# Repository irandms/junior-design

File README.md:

# junior-design
ECE 341 Junior Design - Final Project - Bluetooth controlled AC switch

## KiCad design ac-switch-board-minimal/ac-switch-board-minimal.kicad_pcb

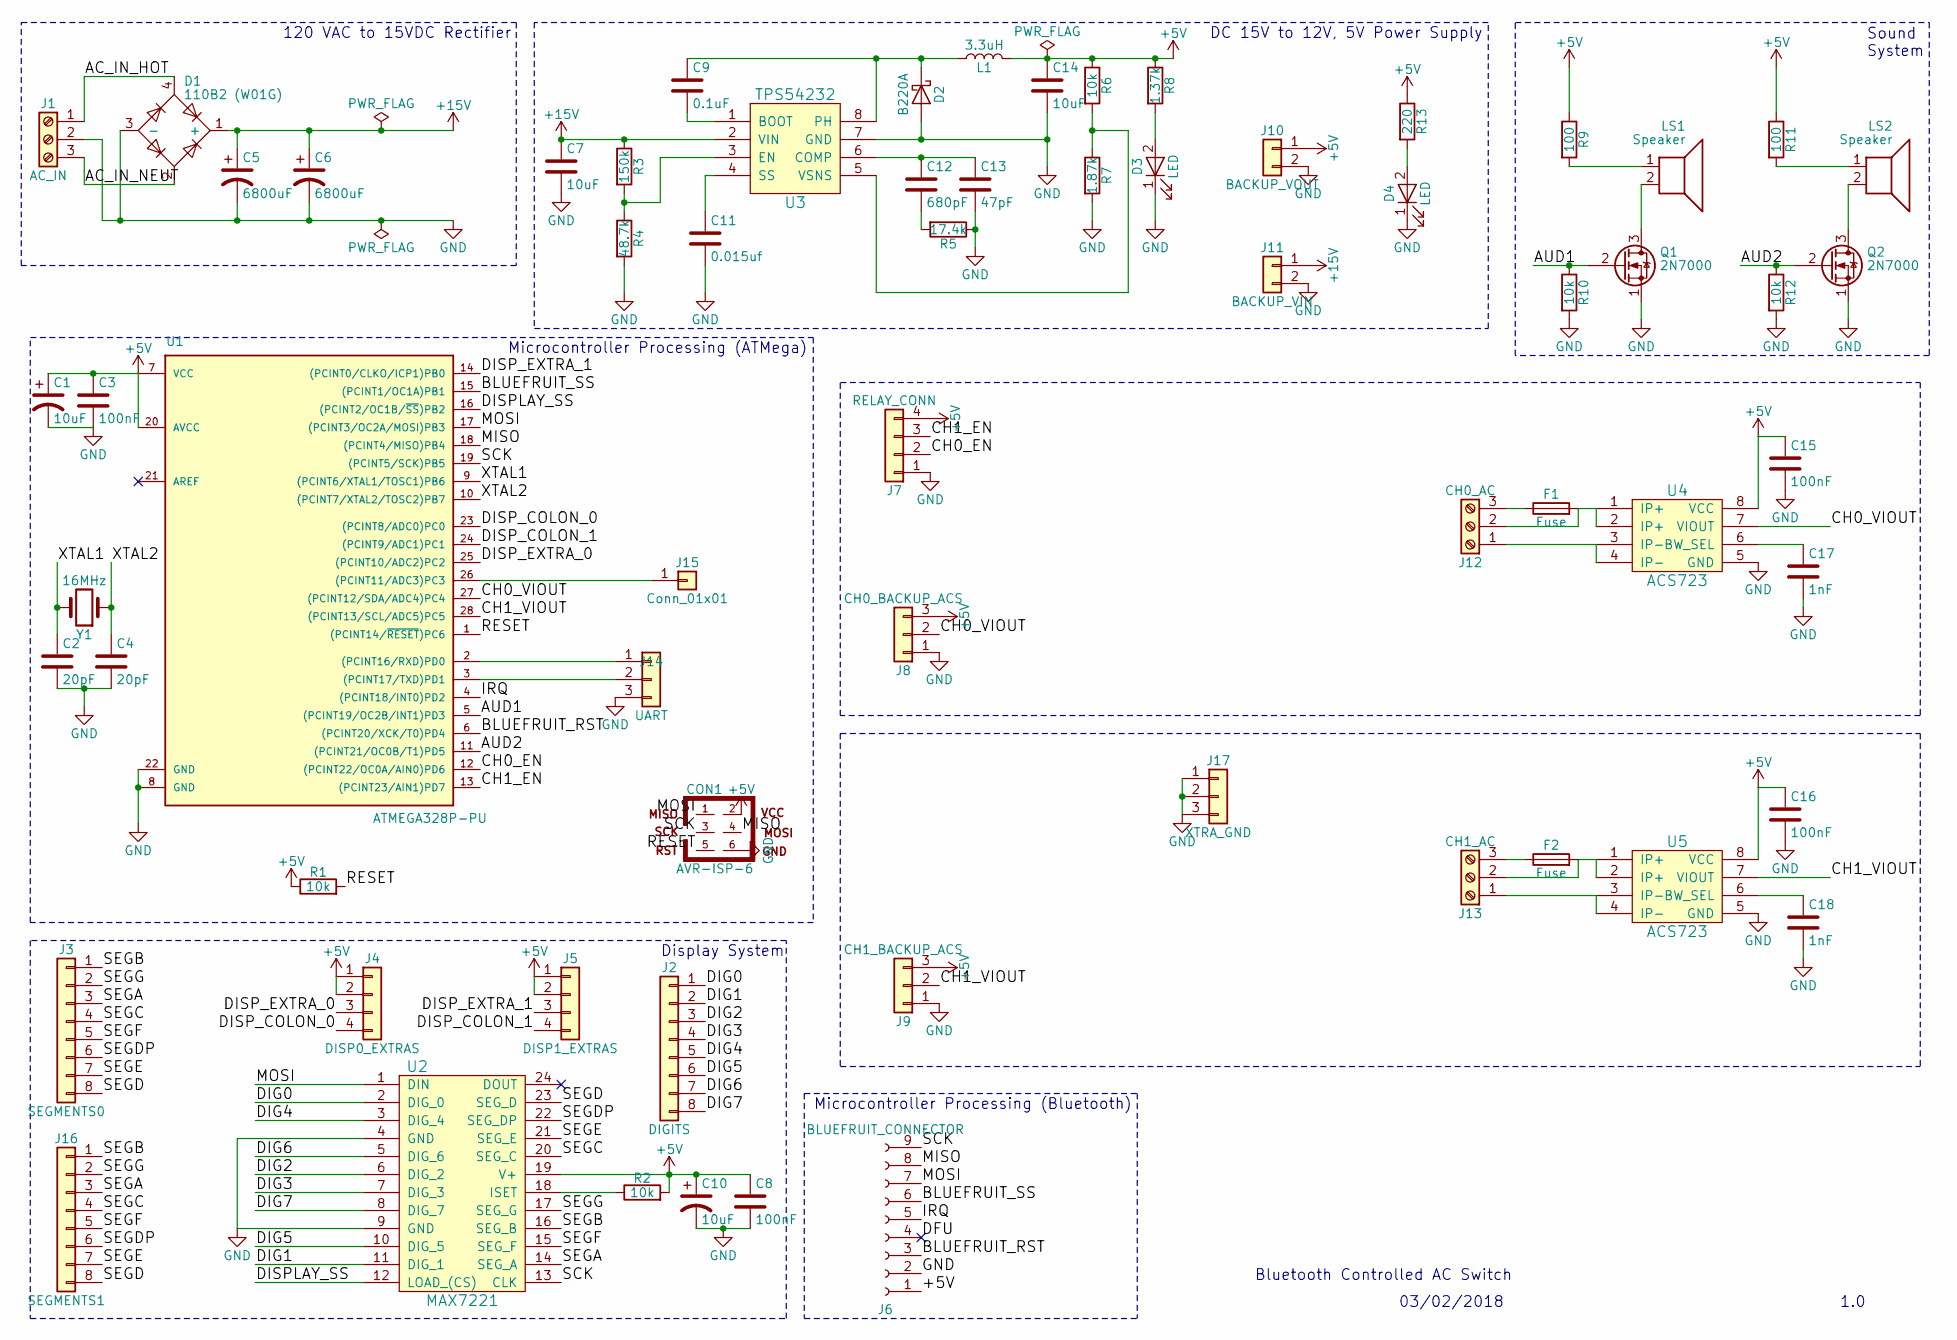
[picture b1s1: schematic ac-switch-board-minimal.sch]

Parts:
C1, C10: 10uF; CP_Elec_4x4.5; MPN EEE-1VA100WR; DigiKey PCE3948CT-ND
C2: 20pF; C_0603; MPN CL10C200JB8NCNC; DigiKey 1276-2220-1-ND
C3, C8, C15, C16: 100nF; C_1206_HandSoldering; MPN C1206C104K5RAC7867; DigiKey 399-1249-1-ND
C4: 20pF; C_0603
C5, C6: 6800uF; CP_Radial_D18.0mm_P7.50mm; MPN EEU-HD1V682; DigiKey P15173-ND
C7: 10uF; C_1206_HandSoldering; MPN C1206C106M3PACTU; DigiKey 399-8153-1-ND
C9: 0.1uF; C_1206_HandSoldering; MPN C1206C104K5RAC7867; DigiKey 399-1249-1-ND
C11: 0.015uf; C_0805_HandSoldering; MPN GRM2195C1H153JA01D; DigiKey 490-1643-1-ND
C12: 680pF; C_0805_HandSoldering; MPN CC0805JRNPO9BN681; DigiKey 311-1121-1-ND
C13: 47pF; C_0805_HandSoldering; MPN CC0805JRNPO9BN470; DigiKey 311-1107-1-ND
C14: 10uF; C_1206_HandSoldering; MPN CL31B106MOHNNNE; DigiKey 1276-6641-1-ND
C17, C18: 1nF; C_0805_HandSoldering; MPN C0805C102K5RACTU; DigiKey 399-1147-1-ND
CON1: AVR-ISP-6; IDC_Header_Straight_6pins
D1: 110B2 (W01G); Diode_Bridge_Round_D8.9mm; MPN W01G-E4/51; DigiKey W01G-E4/51GI-ND
D2: B220A; D_SMA; MPN B220A-13-F; DigiKey B220A-FDICT-ND
D3: LED; LED_0603_HandSoldering; MPN SML-D12V1WT86; DigiKey SML-D12V1WT86CT-ND
D4: LED; Pin_Header_Straight_1x02_Pitch2.54mm
F1, F2: Fuse; Fuseholder5x20_horiz_SemiClosed_Casing10x25mm
J1: AC_IN; AK300-3
J2: DIGITS; Pin_Header_Straight_1x08_Pitch2.54mm
J3: SEGMENTS0; Pin_Header_Straight_1x08_Pitch2.54mm
J4: DISP0_EXTRAS; Pin_Header_Straight_1x04_Pitch2.54mm
J5: DISP1_EXTRAS; Pin_Header_Straight_1x04_Pitch2.54mm
J6: BLUEFRUIT_CONNECTOR; Pin_Header_Straight_1x09_Pitch2.54mm
J7: RELAY_CONN; Pin_Header_Straight_1x04_Pitch2.54mm
J8: CH0_BACKUP_ACS; Pin_Header_Straight_1x03_Pitch2.54mm
J9: CH1_BACKUP_ACS; Pin_Header_Straight_1x03_Pitch2.54mm
J10: BACKUP_VOUT; Pin_Header_Straight_1x02_Pitch2.54mm
J11: BACKUP_VIN; Pin_Header_Straight_1x02_Pitch2.54mm
J12: CH0_AC; AK300-3
J13: CH1_AC; AK300-3
J14: UART; Pin_Header_Straight_1x03_Pitch2.54mm
J15: Conn_01x01; Pin_Header_Straight_1x01_Pitch2.54mm
J16: SEGMENTS1; Pin_Header_Straight_1x08_Pitch2.54mm
J17: XTRA_GND; Pin_Header_Straight_1x03_Pitch2.54mm
L1: 3.3uH; L_Sumida_4.9x4.9mm_diag; MPN CDRH4D28CLDNP-3R3PC; DigiKey 308-2037-1-ND
LS1, LS2: Speaker; Pin_Header_Straight_1x02_Pitch2.54mm
Q1, Q2: 2N7000; TO-92_Molded_Narrow
R1, R2, R6, R10, R12: 10k; R_0805_HandSoldering; MPN ERA-6AEB103V; DigiKey P10KDACT-ND
R3: 150k; R_0805_HandSoldering; MPN RR1220P-154-D; DigiKey RR12P150KDCT-ND
R4: 48.7k; R_0805_HandSoldering; MPN RC0805FR-0748K7L; DigiKey 311-48.7KCRCT-ND
R5: 17.4k; R_0805_HandSoldering; MPN RC0805FR-0717K4L; DigiKey 311-17.4KCRCT-ND
R7: 1.87k; R_0805_HandSoldering; MPN RC0805FR-071K87L; DigiKey 311-1.87KCRCT-ND
R8: 1.37k; R_0805_HandSoldering; MPN RC0805FR-071K37L; DigiKey 311-1.37KCRCT-ND
R9, R11: 100; R_Axial_DIN0207_L6.3mm_D2.5mm_P5.08mm_Vertical
R13: 220; R_0805_HandSoldering; MPN ESR10EZPJ221; DigiKey RHM220KCT-ND
U1: ATMEGA328P-PU; DIP-28_W7.62mm_Socket
U2: MAX7221; DIP-24_W7.62mm_Socket
U3: TPS54232; SOIC-8-N; MPN TPS54232DR; DigiKey 296-39414-1-ND
U4, U5: ACS723; SOIC-8-N; MPN ACS723LLCTR-05AB-T; DigiKey 620-1641-1-ND
Y1: 16MHz; Crystal_HC49-4H_Vertical

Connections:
+5V: C1.1, C3.1, C8.1, C10.1, C14.1, C15.1, C16.1, CON1.2, J4.1, J4.2, J5.1, J5.2, J6.1, J7.4, J8.3, J9.3, J10.1, L1.2, R1.1, R2.2, R6.1, R8.1, R9.1, R11.1, R13.1, U1.7 (VCC), U1.20 (AVCC), U2.19 (V+), U4.8 (VCC), U5.8 (VCC)
+15V: C5.1, C6.1, C7.1, D1.1 (+), J11.1, R3.1, U3.2 (VIN)
/AC_IN_HOT: D1.4, J1.1
/AC_IN_NEUT: D1.2, J1.3
/AUD1: Q1.2 (G), R10.1, U1.5 ((PCINT19/OC2B/INT1)PD3)
/AUD2: Q2.2 (G), R12.1, U1.11 ((PCINT21/OC0B/T1)PD5)
/BLUEFRUIT_RST: J6.3, U1.6 ((PCINT20/XCK/T0)PD4)
/BLUEFRUIT_SS: J6.6, U1.15 ((PCINT1/OC1A)PB1)
/CH0_EN: J7.2, U1.12 ((PCINT22/OC0A/AIN0)PD6)
/CH0_VIOUT: J8.2, U1.27 ((PCINT12/SDA/ADC4)PC4), U4.7 (VIOUT)
/CH1_EN: J7.3, U1.13 ((PCINT23/AIN1)PD7)
/CH1_VIOUT: J9.2, U1.28 ((PCINT13/SCL/ADC5)PC5), U5.7 (VIOUT)
/DFU: J6.4
/DIG0: J2.1, U2.2 (DIG_0)
/DIG1: J2.2, U2.11 (DIG_1)
/DIG2: J2.3, U2.6 (DIG_2)
/DIG3: J2.4, U2.7 (DIG_3)
/DIG4: J2.5, U2.3 (DIG_4)
/DIG5: J2.6, U2.10 (DIG_5)
/DIG6: J2.7, U2.5 (DIG_6)
/DIG7: J2.8, U2.8 (DIG_7)
/DISPLAY_SS: U1.16 ((PCINT2/OC1B/~SS~)PB2), U2.12 (LOAD_(CS))
/DISP_COLON_0: J4.4, U1.23 ((PCINT8/ADC0)PC0)
/DISP_COLON_1: J5.4, U1.24 ((PCINT9/ADC1)PC1)
/DISP_EXTRA_0: J4.3, U1.25 ((PCINT10/ADC2)PC2)
/DISP_EXTRA_1: J5.3, U1.14 ((PCINT0/CLKO/ICP1)PB0)
/IRQ: J6.5, U1.4 ((PCINT18/INT0)PD2)
/RESET: CON1.5, R1.2, U1.1 ((PCINT14/~RESET~)PC6)
/SCK: CON1.3, J6.9, U1.19 ((PCINT5/SCK)PB5), U2.13 (CLK)
/SEGA: J3.3, J16.3, U2.14 (SEG_A)
/SEGB: J3.1, J16.1, U2.16 (SEG_B)
/SEGC: J3.4, J16.4, U2.20 (SEG_C)
/SEGD: J3.8, J16.8, U2.23 (SEG_D)
/SEGDP: J3.6, J16.6, U2.22 (SEG_DP)
/SEGE: J3.7, J16.7, U2.21 (SEG_E)
/SEGF: J3.5, J16.5, U2.15 (SEG_F)
/SEGG: J3.2, J16.2, U2.17 (SEG_G)
/XTAL1: C2.1, U1.9 ((PCINT6/XTAL1/TOSC1)PB6), Y1.2
/XTAL2: C4.1, U1.10 ((PCINT7/XTAL2/TOSC2)PB7), Y1.1
GND: C1.2, C2.2, C3.2, C4.2, C5.2, C6.2, C7.2, C8.2, C10.2, C11.2, C13.2, C14.2, C15.2, C16.2, C17.2, C18.2, CON1.6, D1.3 (-), D2.2 (A), D3.1 (K), D4.1 (K), J1.2, J6.2, J7.1, J8.1, J9.1, J10.2, J11.2, J14.3, J17.1, J17.2, J17.3, Q1.1 (S), Q2.1 (S), R4.2, R5.1, R7.2, R10.2, R12.2, U1.8 (GND), U1.22 (GND), U2.4 (GND), U2.9 (GND), U3.7 (GND), U4.5 (GND), U5.5 (GND)
unnamed: C9.1, D2.1 (K), L1.1, U3.8 (PH)
unnamed: C9.2, U3.1 (BOOT)
unnamed: C11.1, U3.4 (SS)
unnamed: C12.1, C13.1, U3.6 (COMP)
unnamed: C12.2, R5.2
unnamed: C17.1, U4.6 (BW_SEL)
unnamed: C18.1, U5.6 (BW_SEL)
unnamed: D3.2 (A), R8.2
unnamed: D4.2 (A), R13.2
unnamed: F1.1, J12.3
unnamed: F1.2, J12.2, U4.1 (IP+), U4.2 (IP+)
unnamed: F2.1, J13.3
unnamed: F2.2, J13.2, U5.1 (IP+), U5.2 (IP+)
unnamed: J12.1, U4.3 (IP-), U4.4 (IP-)
unnamed: J13.1, U5.3 (IP-), U5.4 (IP-)
unnamed: J14.1, U1.2 ((PCINT16/RXD)PD0)
unnamed: J14.2, U1.3 ((PCINT17/TXD)PD1)
unnamed: J15.1, U1.26 ((PCINT11/ADC3)PC3)
unnamed: LS1.1, R9.2
unnamed: LS1.2, Q1.3 (D)
unnamed: LS2.1, R11.2
unnamed: LS2.2, Q2.3 (D)
unnamed: R2.1, U2.18 (ISET)
unnamed: R3.2, R4.1, U3.3 (EN)
unnamed: R6.2, R7.1, U3.5 (VSNS)

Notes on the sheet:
Bluetooth Controlled AC Switch
03/02/2018
1.0
Microcontroller Processing (ATMega)
Microcontroller Processing (Bluetooth)
Display System
Sound System
120 VAC to 15VDC Rectifier
DC 15V to 12V, 5V Power Supply

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
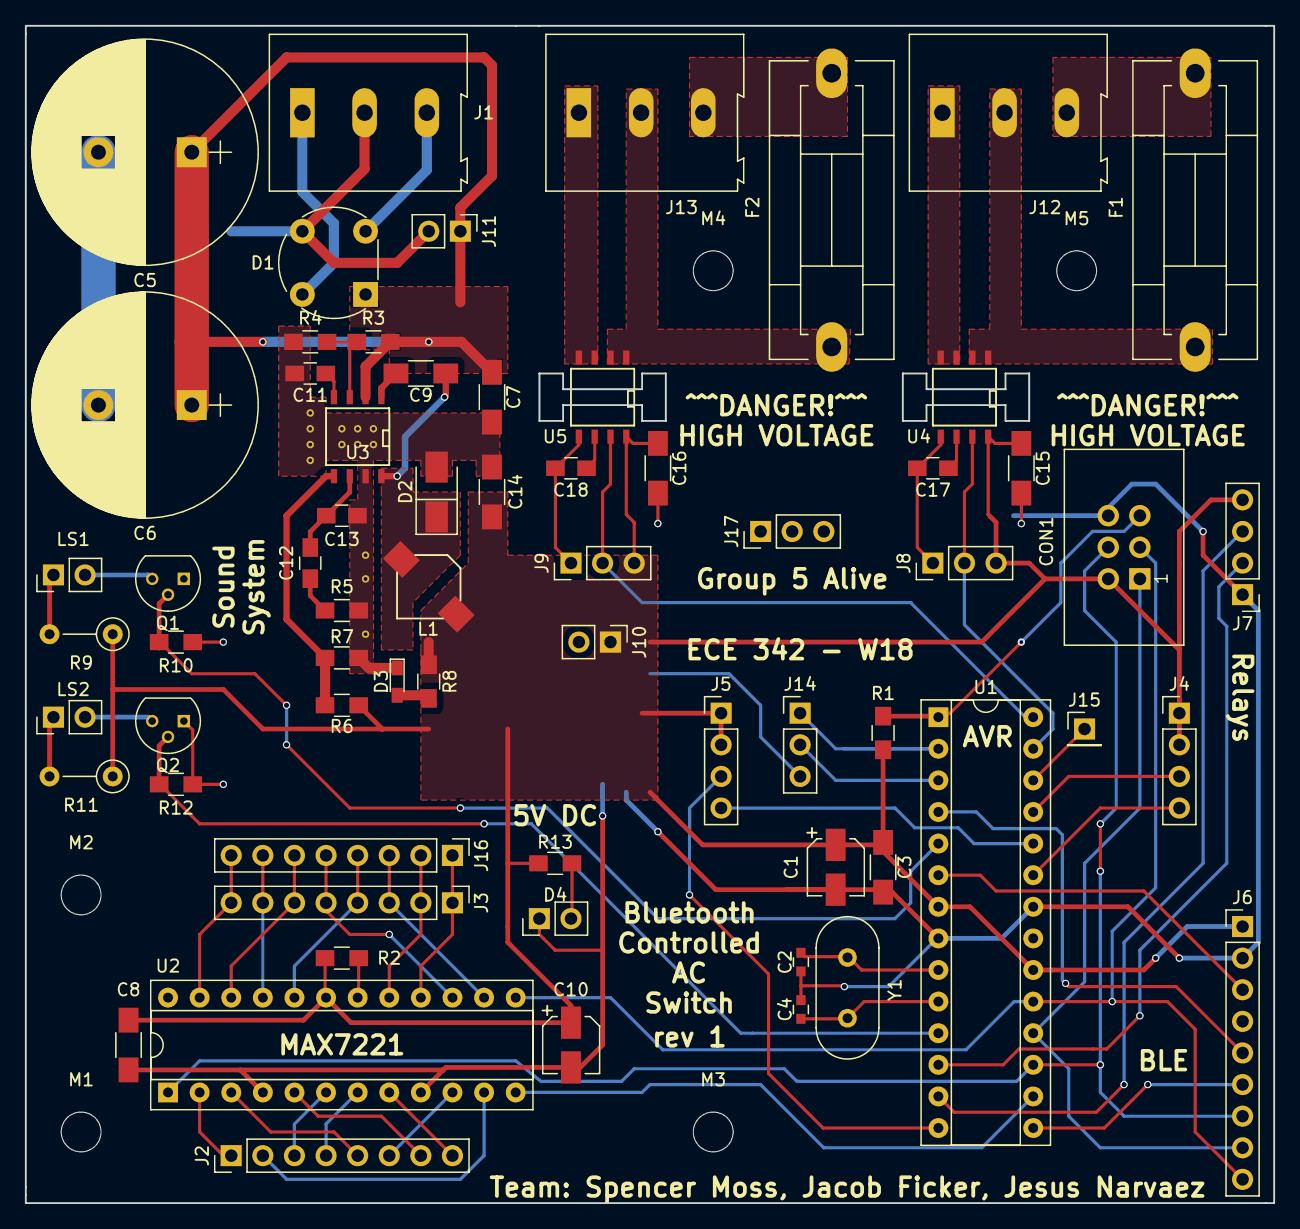
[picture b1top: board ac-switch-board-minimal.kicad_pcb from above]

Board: 2 copper layers, 100.3 x 94.6 mm, 71 parts (0 on the bottom side), 66 nets.

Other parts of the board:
M1, M2, M3, M4, M5: MountingHole_3.2mm_M3

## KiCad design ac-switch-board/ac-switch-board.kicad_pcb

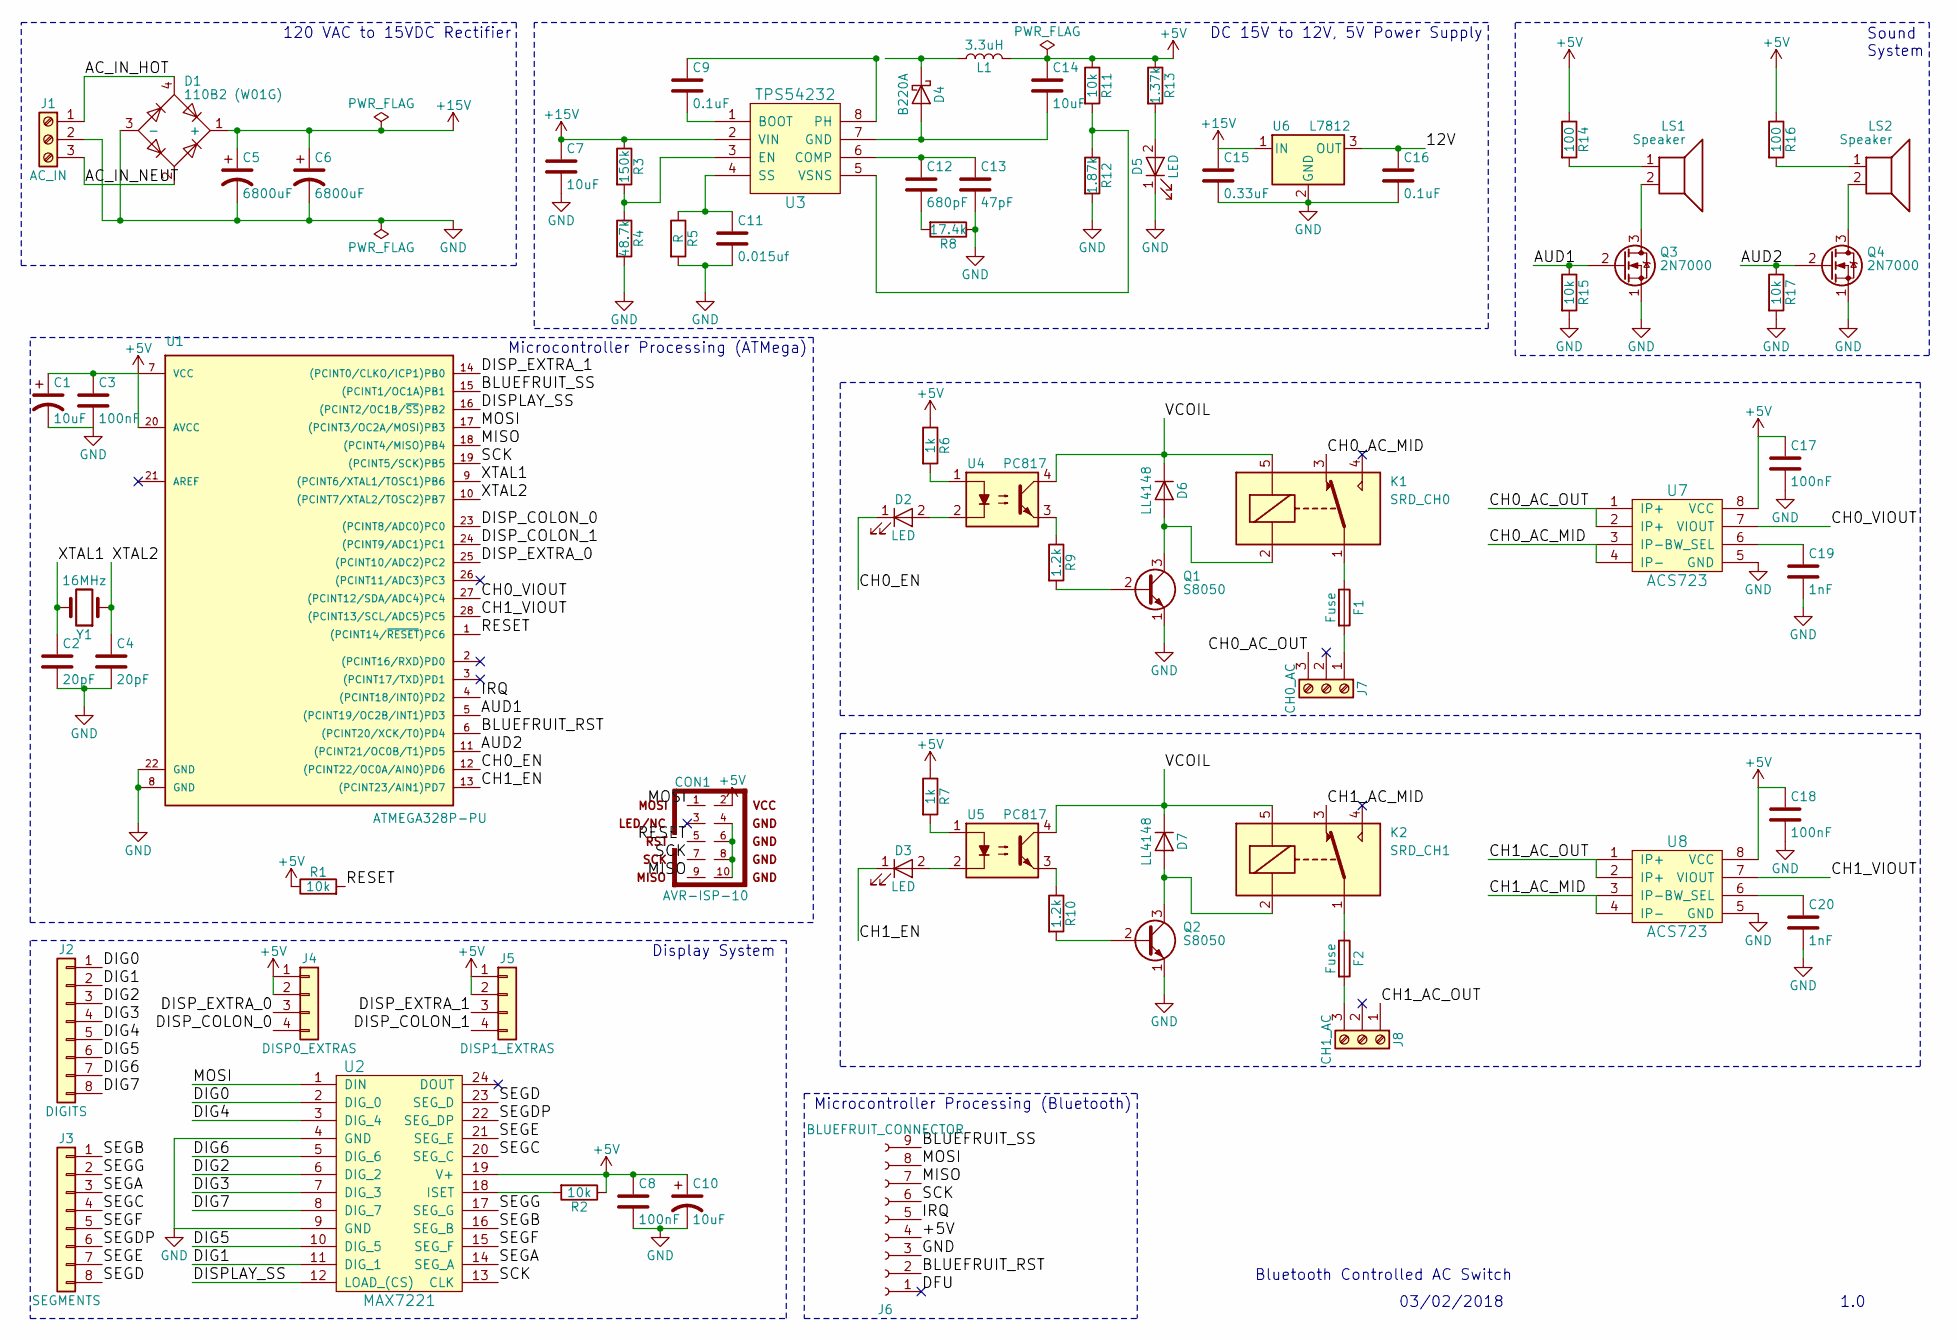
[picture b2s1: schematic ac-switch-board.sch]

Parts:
C1, C10: 10uF; CP_Elec_4x4.5
C2, C4: 20pF; C_0603
C3, C8, C17, C18: 100nF; C_1206_HandSoldering
C5, C6: 6800uF; CP_Radial_D18.0mm_P7.50mm
C7, C14: 10uF; C_1206_HandSoldering
C9: 0.1uF; C_1206_HandSoldering
C11: 0.015uf; C_0805_HandSoldering
C12: 680pF; C_0805_HandSoldering
C13: 47pF; C_0805_HandSoldering
C15: 0.33uF; C_0805_HandSoldering
C16: 0.1uF; C_0805_HandSoldering
C19, C20: 1nF; C_0805_HandSoldering
CON1: AVR-ISP-10; IDC_Header_Straight_10pins
D1: 110B2 (W01G); Diode_Bridge_Round_D8.9mm
D2, D3, D5: LED; LED_0603_HandSoldering; DigiKey SML-D12V1WT86
D4: B220A; D_SMA
D6, D7: LL4148; D_MiniMELF
F1, F2: Fuse; Fuseholder5x20_horiz_SemiClosed_Casing10x25mm
J1: AC_IN; AK300-3
J2: DIGITS; Pin_Header_Straight_1x08_Pitch2.54mm
J3: SEGMENTS; Pin_Header_Straight_1x08_Pitch2.54mm
J4: DISP0_EXTRAS; Pin_Header_Straight_1x04_Pitch2.54mm
J5: DISP1_EXTRAS; Pin_Header_Straight_1x04_Pitch2.54mm
J6: BLUEFRUIT_CONNECTOR; Pin_Header_Straight_1x09_Pitch2.54mm
J7: CH0_AC; AK300-3
J8: CH1_AC; AK300-3
K1: SRD_CH0; Relay_SPDT_SANYOU_SRD_Series_Form_C
K2: SRD_CH1; Relay_SPDT_SANYOU_SRD_Series_Form_C
L1: 3.3uH; L_Sumida_4.9x4.9mm_diag
LS1, LS2: Speaker; Pin_Header_Straight_1x02_Pitch2.54mm
Q1, Q2: S8050; TO-92_Molded_Narrow
Q3, Q4: 2N7000; TO-92_Molded_Narrow
R1, R2, R11, R15, R17: 10k; R_0805_HandSoldering
R3: 150k; R_0805_HandSoldering
R4: 48.7k; R_0805_HandSoldering
R5: R; R_0805_HandSoldering
R6, R7: 1k; R_0805_HandSoldering
R8: 17.4k; R_0805_HandSoldering
R9, R10: 1.2k; R_0805_HandSoldering
R12: 1.87k; R_0805_HandSoldering
R13: 1.37k; R_0805_HandSoldering
R14, R16: 100; R_Axial_DIN0207_L6.3mm_D2.5mm_P10.16mm_Horizontal
U1: ATMEGA328P-PU; DIP-28_W7.62mm_Socket
U2: MAX7221; DIP-24_W7.62mm_Socket
U3: TPS54232; SOIC-8-N
U4, U5: PC817; DIP-4_W7.62mm
U6: L7812; TO-220_Vertical
U7, U8: ACS723; SOIC-8-N
Y1: 16MHz; Crystal_HC49-4H_Vertical

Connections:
+5V: C1.1, C3.1, C8.1, C10.1, C14.1, C17.1, C18.1, CON1.2, J4.1, J4.2, J5.1, J5.2, J6.4, L1.2, R1.1, R2.1, R6.1, R7.1, R11.1, R13.1, R14.1, R16.1, U1.7 (VCC), U1.20 (AVCC), U2.19 (V+), U7.8 (VCC), U8.8 (VCC)
+15V: C5.1, C6.1, C7.1, C15.1, D1.1 (+), R3.1, U3.2 (VIN), U6.1 (IN)
/12V: C16.1, U6.3 (OUT)
/AC_IN_HOT: D1.4, J1.1
/AC_IN_NEUT: D1.2, J1.3
/AUD1: Q3.2 (G), R15.1, U1.5 ((PCINT19/OC2B/INT1)PD3)
/AUD2: Q4.2 (G), R17.1, U1.11 ((PCINT21/OC0B/T1)PD5)
/BLUEFRUIT_RST: J6.2, U1.6 ((PCINT20/XCK/T0)PD4)
/BLUEFRUIT_SS: J6.9, U1.15 ((PCINT1/OC1A)PB1)
/CH0_AC_MID: K1.3, U7.3 (IP-), U7.4 (IP-)
/CH0_AC_OUT: J7.3, U7.1 (IP+), U7.2 (IP+)
/CH0_EN: D2.1 (K), U1.12 ((PCINT22/OC0A/AIN0)PD6)
/CH0_VIOUT: U1.27 ((PCINT12/SDA/ADC4)PC4), U7.7 (VIOUT)
/CH1_AC_MID: K2.3, U8.3 (IP-), U8.4 (IP-)
/CH1_AC_OUT: J8.1, U8.1 (IP+), U8.2 (IP+)
/CH1_EN: D3.1 (K), U1.13 ((PCINT23/AIN1)PD7)
/CH1_VIOUT: U1.28 ((PCINT13/SCL/ADC5)PC5), U8.7 (VIOUT)
/DFU: J6.1
/DIG0: J2.1, U2.2 (DIG_0)
/DIG1: J2.2, U2.11 (DIG_1)
/DIG2: J2.3, U2.6 (DIG_2)
/DIG3: J2.4, U2.7 (DIG_3)
/DIG4: J2.5, U2.3 (DIG_4)
/DIG5: J2.6, U2.10 (DIG_5)
/DIG6: J2.7, U2.5 (DIG_6)
/DIG7: J2.8, U2.8 (DIG_7)
/DISPLAY_SS: U1.16 ((PCINT2/OC1B/~SS~)PB2), U2.12 (LOAD_(CS))
/DISP_COLON_0: J4.4, U1.23 ((PCINT8/ADC0)PC0)
/DISP_COLON_1: J5.4, U1.24 ((PCINT9/ADC1)PC1)
/DISP_EXTRA_0: J4.3, U1.25 ((PCINT10/ADC2)PC2)
/DISP_EXTRA_1: J5.3, U1.14 ((PCINT0/CLKO/ICP1)PB0)
/IRQ: J6.5, U1.4 ((PCINT18/INT0)PD2)
/MISO: CON1.9, J6.7, U1.18 ((PCINT4/MISO)PB4)
/MOSI: CON1.1, J6.8, U1.17 ((PCINT3/OC2A/MOSI)PB3), U2.1 (DIN)
/RESET: CON1.5, R1.2, U1.1 ((PCINT14/~RESET~)PC6)
/SCK: CON1.7, J6.6, U1.19 ((PCINT5/SCK)PB5), U2.13 (CLK)
/SEGA: J3.3, U2.14 (SEG_A)
/SEGB: J3.1, U2.16 (SEG_B)
/SEGC: J3.4, U2.20 (SEG_C)
/SEGD: J3.8, U2.23 (SEG_D)
/SEGDP: J3.6, U2.22 (SEG_DP)
/SEGE: J3.7, U2.21 (SEG_E)
/SEGF: J3.5, U2.15 (SEG_F)
/SEGG: J3.2, U2.17 (SEG_G)
/VCOIL: D6.1 (K), D7.1 (K), K1.5, K2.5, U4.4, U5.4
/XTAL1: C2.1, U1.9 ((PCINT6/XTAL1/TOSC1)PB6), Y1.2
/XTAL2: C4.1, U1.10 ((PCINT7/XTAL2/TOSC2)PB7), Y1.1
GND: C1.2, C2.2, C3.2, C4.2, C5.2, C6.2, C7.2, C8.2, C10.2, C11.2, C13.2, C15.2, C16.2, C17.2, C18.2, C19.2, C20.2, D1.3 (-), D5.1 (K), J1.2, J6.3, Q1.1 (E), Q2.1 (E), Q3.1 (S), Q4.1 (S), R4.2, R5.2, R8.1, R12.2, R15.2, R17.2, U1.8 (GND), U1.22 (GND), U2.4 (GND), U2.9 (GND), U6.2 (GND), U7.5 (GND), U8.5 (GND)
unnamed: C9.1, U3.8 (PH)
unnamed: C9.2, U3.1 (BOOT)
unnamed: C11.1, R5.1, U3.4 (SS)
unnamed: C12.1, C13.1, U3.6 (COMP)
unnamed: C12.2, R8.2
unnamed: C14.2, D4.2 (A), U3.7 (GND)
unnamed: C19.1, U7.6 (BW_SEL)
unnamed: C20.1, U8.6 (BW_SEL)
unnamed: CON1.4, CON1.6, CON1.8, CON1.10
unnamed: D2.2 (A), U4.2
unnamed: D3.2 (A), U5.2
unnamed: D4.1 (K), L1.1
unnamed: D5.2 (A), R13.2
unnamed: D6.2 (A), K1.2, Q1.3 (C)
unnamed: D7.2 (A), K2.2, Q2.3 (C)
unnamed: F1.1, K1.1
unnamed: F1.2, J7.1
unnamed: F2.1, K2.1
unnamed: F2.2, J8.3
unnamed: LS1.1, R14.2
unnamed: LS1.2, Q3.3 (D)
unnamed: LS2.1, R16.2
unnamed: LS2.2, Q4.3 (D)
unnamed: Q1.2 (B), R9.2
unnamed: Q2.2 (B), R10.2
unnamed: R2.2, U2.18 (ISET)
unnamed: R3.2, R4.1, U3.3 (EN)
unnamed: R6.2, U4.1
unnamed: R7.2, U5.1
unnamed: R9.1, U4.3
unnamed: R10.1, U5.3
unnamed: R11.2, R12.1, U3.5 (VSNS)

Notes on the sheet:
Bluetooth Controlled AC Switch
03/02/2018
1.0
Microcontroller Processing (ATMega)
Microcontroller Processing (Bluetooth)
Display System
Sound System
120 VAC to 15VDC Rectifier
DC 15V to 12V, 5V Power Supply

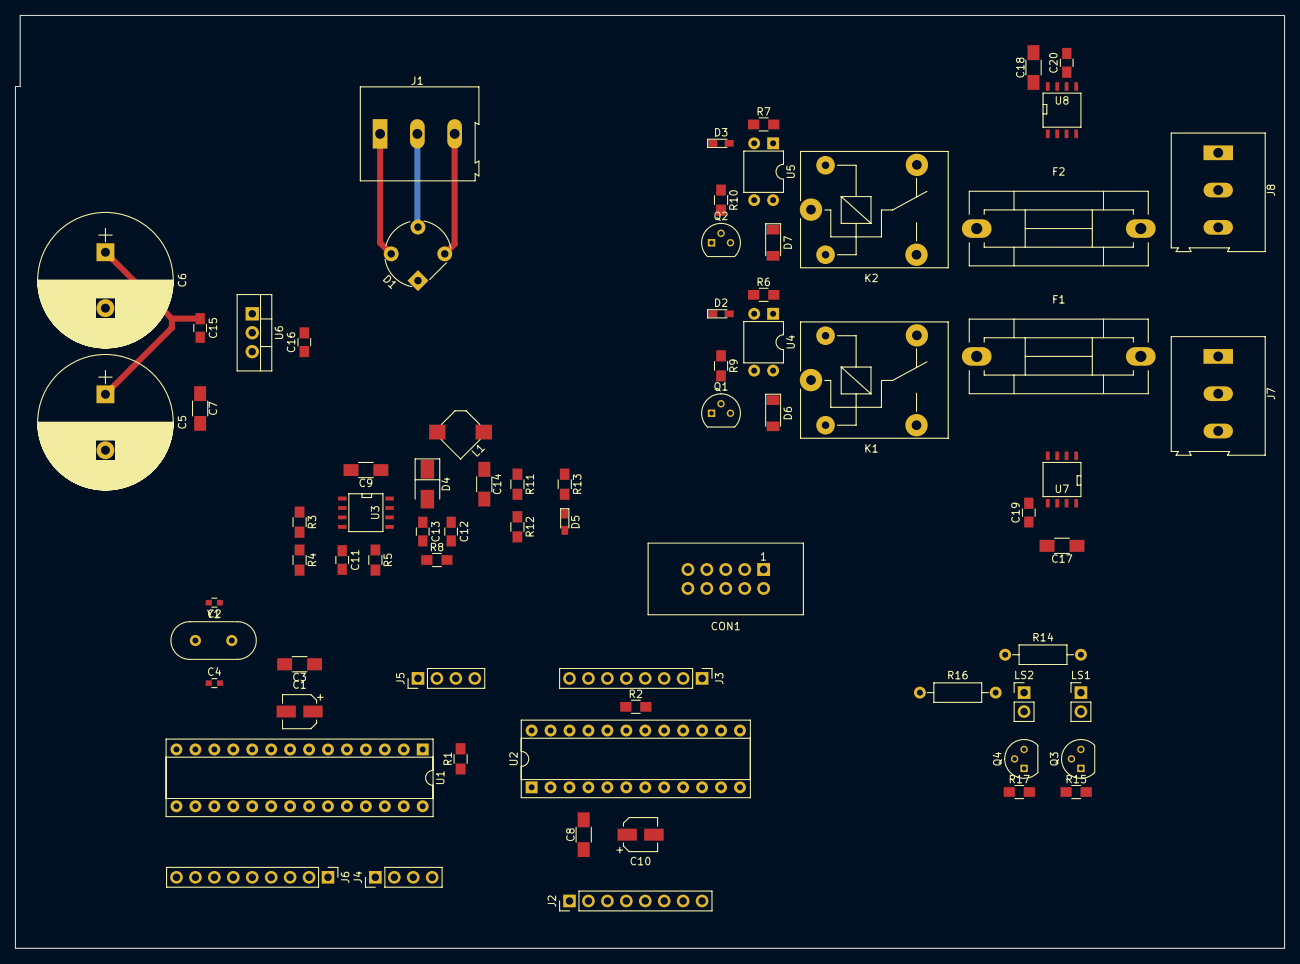
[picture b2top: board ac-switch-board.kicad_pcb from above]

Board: 2 copper layers, 170.2 x 125.1 mm, 73 parts (0 on the bottom side), 79 nets.

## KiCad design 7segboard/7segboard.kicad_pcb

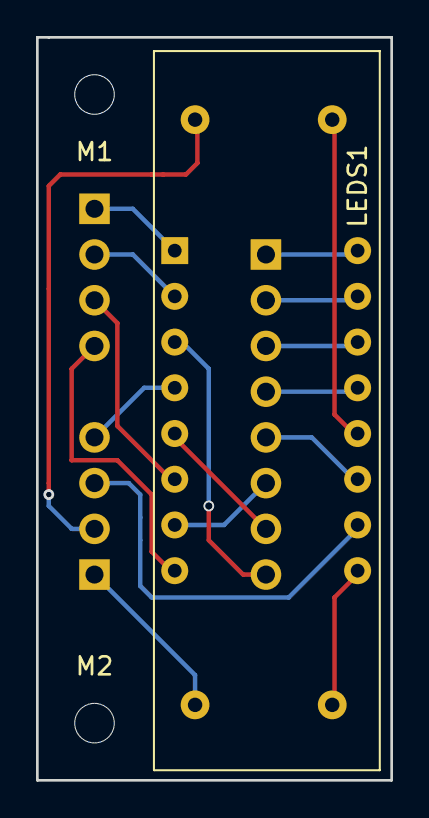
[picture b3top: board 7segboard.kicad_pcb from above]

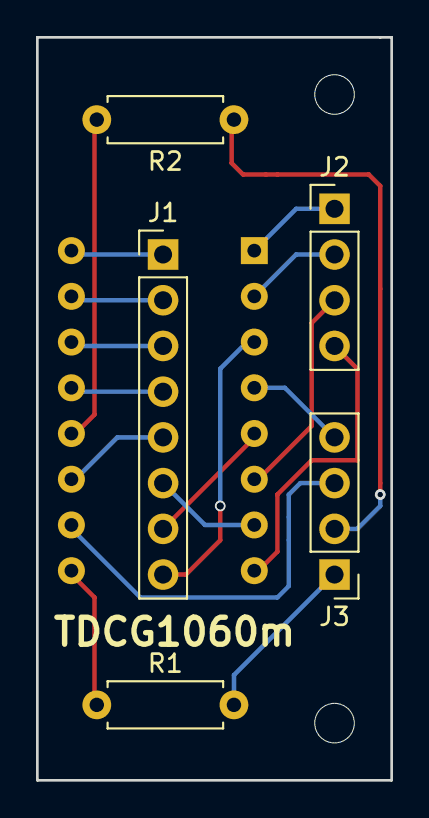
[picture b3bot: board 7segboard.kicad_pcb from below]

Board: 2 copper layers, 19.7 x 41.3 mm, 8 parts (5 on the bottom side), 18 nets.

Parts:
J1: SEGMENTS; Pin_Header_Straight_1x08_Pitch2.54mm
J2: DIGITS; Pin_Header_Straight_1x04_Pitch2.54mm
J3: EXTRAS; Pin_Header_Straight_1x04_Pitch2.54mm
LEDS1: TDCFG1060m; TDCG1060m
M1: M1; MountingHole_2.2mm_M2
M2: M2; MountingHole_2.2mm_M2
R1, R2: 330; R_Axial_DIN0207_L6.3mm_D2.5mm_P7.62mm_Horizontal

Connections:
/COLON: J3.4, LEDS1.4
/COLON_RET: LEDS1.12, R2.2
/DIG0: J2.1, LEDS1.1
/DIG1: J2.2, LEDS1.2
/DIG2: J2.3, LEDS1.6
/DIG3: J2.4, LEDS1.8
/EXTRA: J3.3, LEDS1.10
/EXTRA_RET: LEDS1.9, R1.1
/SEGA: J1.3, LEDS1.14
/SEGB: J1.1, LEDS1.16
/SEGC: J1.4, LEDS1.13
/SEGD: J1.8, LEDS1.3
/SEGDP: J1.6, LEDS1.7
/SEGE: J1.7, LEDS1.5
/SEGF: J1.5, LEDS1.11
/SEGG: J1.2, LEDS1.15
unnamed: J3.1, R1.2
unnamed: J3.2, R2.1

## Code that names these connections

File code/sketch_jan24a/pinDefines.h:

#pragma once

/*
 * I/O pin definitions
 */ 

// BLUEFRUIT/BLUETOOTH COMM
#define BLUEFRUIT_SPI_CS               9
#define BLUEFRUIT_SPI_IRQ              2
#define BLUEFRUIT_SPI_RST              4    // Optional but recommended, set to -1 if unused

// SOUND SYSTEM
#define SPEAKER1_PIN                  PD5
#define SPEAKER2_PIN                  PD3
#define SPEAKER1_DDR                  DDRD
#define SPEAKER2_DDR                  DDRD
#define SPEAKER1_PORT                 PORTD
#define SPEAKER2_PORT                 PORTD

// DISPLAY SYSTEM
#define DISPLAY_SS                    10
#define CH0_COLON_PIN                 A0
#define CH1_COLON_PIN                 A1
#define CH0_DISP_PIN                  A2
#define CH1_DISP_PIN                  8 

// AC CHANNELS
#define CH_DDR                        DDRD
#define CH_PORT                       PORTD
#define CH0_EN_PIN                    PD6
#define CH1_EN_PIN                    PD7

// A4, A5
#define CH0_READ_PIN                  4
#define CH1_READ_PIN                  5

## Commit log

2017-11-14 Create Questions and engineering requirements
2017-11-15 Create Stakeholder meeting 11_14_17
2017-11-19 Adding links to some possible materials and resources
2017-11-30 Restructured repository, added Block Diagram and Engineering Requirements
2017-11-30 Updated materials list
2018-01-16 Create Week 12 Guidance Meeting
2018-01-25 Adding code for the main mcu
2018-01-25 Timer is working well with relay control
2018-01-25 Create Bill of Materials (Tentative)
2018-01-26 integrated sound system into main program
2018-01-30 Create Guidance Meeting 2
2018-02-03 Integrated AC Current Sense and Control, Sound System, Timer code
2018-02-03 Board design things
2018-02-03 Moved speakers to B channels of their timers, moved toggle to software interrupt. Added display code, working with maxim and 7segs
2018-02-05 Main program works with all hardware
2018-02-09 Updated board, added datasheets
2018-02-09 board progress
2018-02-10 board completely routed
2018-02-10 Added silkscreen info
2018-02-11 Commented code
2018-02-13 Refactored some code, more integration work. Display system can now show timer duration
2018-02-13 More small board tweaks
2018-02-16 Board work
2018-03-02 App Code
    These are just the java files. The gradle scripts are not included, but they need to be configured correctly.
2018-03-08 Board things, including errata list for next version
2018-03-08 bluetooth packet parsing is up
2018-03-08 board adds
2018-03-08 removing unnecessary serial debug statements
2018-03-10 Cleanup bluetooth, recalibrated for new ACS723 sensors, fixed issues with display mode showing colon after timer expiration
